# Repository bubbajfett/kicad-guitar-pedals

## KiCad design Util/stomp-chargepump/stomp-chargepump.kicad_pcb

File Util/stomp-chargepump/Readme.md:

# Chargepump/stomp board.

*  prevents reverse polarity
*  3pdt + led
*  -9v optional out
*  18v optional out
*  Both ICL7660 and LT1054

This has been tested but not thoroughly.    This layout is based on
several vero layout on Tagboardeffects.blogspot.com

2nd revision of this to use 4pin connectors for wiring simplicity

All registered trademarks are owned by their respective owners.

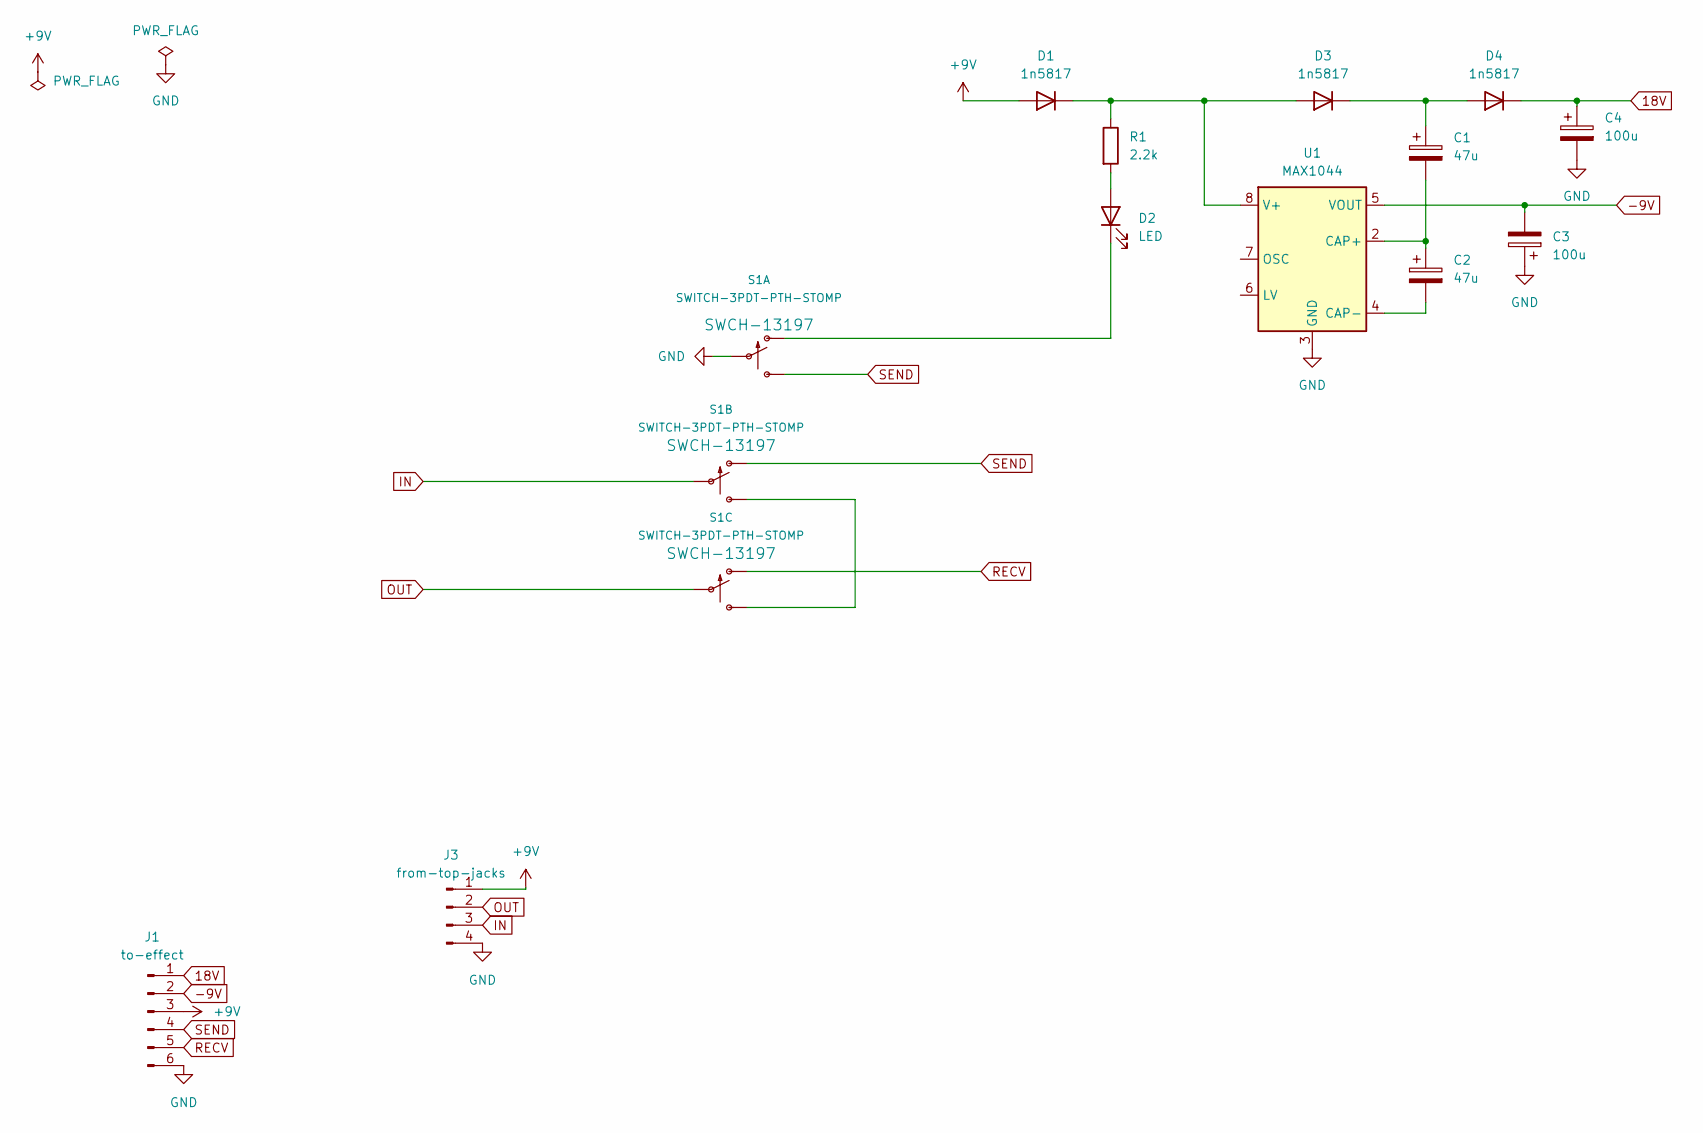
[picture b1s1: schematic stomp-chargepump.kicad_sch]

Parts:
C1, C2: 47u; CP_Radial_D5.0mm_P2.00mm
C3, C4: 100u; CP_Radial_D6.3mm_P2.50mm
D1, D3, D4: 1n5817; D_5W_P10.16mm_Horizontal
D2: LED; LED_D3.0mm
J1: to-effect; PinHeader_1x06_P2.54mm_Vertical
J3: from-top-jacks; PinHeader_1x04_P2.54mm_Vertical
R1: 2.2k; R_Axial_DIN0207_L6.3mm_D2.5mm_P10.16mm_Horizontal
S1: SWITCH-3PDT-PTH-STOMP; STOMP_SWITCH_3PDT
U1: MAX1044; DIP-8_W7.62mm_LongPads

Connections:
18V: C4.1, D4.1 (K), J1.1
+9V: D1.2 (A), J1.3, J3.1
-9V: C3.2, J1.2, U1.5 (VOUT)
GND: C3.1, C4.2, J1.6, J3.4, S1.P$2, U1.3 (GND)
IN: J3.3, S1.P$5
unnamed: D1.1 (K), D3.2 (A), R1.1, U1.8 (V+)
unnamed: D2.2 (A), R1.2
unnamed: D2.1 (K), S1.P$1 (O)
unnamed: C1.1, D3.1 (K), D4.2 (A)
unnamed: S1.P$6 (S), S1.P$9 (S)
unnamed: C1.2, C2.1, U1.2 (CAP+)
unnamed: C2.2, U1.4 (CAP-)
OUT: J3.2, S1.P$8
RECV: J1.5, S1.P$7 (O)
SEND: J1.4, S1.P$3 (S), S1.P$4 (O)

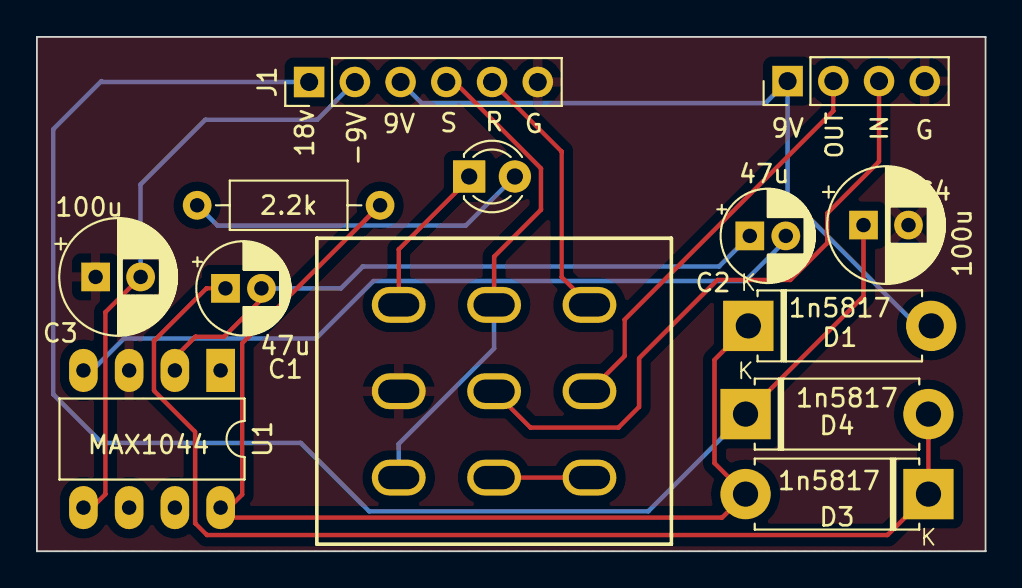
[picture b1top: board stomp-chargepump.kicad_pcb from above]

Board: 2 copper layers, 52.7 x 28.6 mm, 13 parts (0 on the bottom side), 15 nets.

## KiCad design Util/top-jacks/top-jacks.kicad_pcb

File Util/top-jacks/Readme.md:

# TOP Jacks

This is a pcb allowing the input, output and power jack to be mounted at the top of the enclosure, instead of having power at the top, and jacks mounted on the side.   This simplifies the wiring.   I put the diode on this as well so that all pedals get polarity protection.   The jacks used from taydaelectronics: 

6.35mm 1/4" Right Angle Mono Female Connector Thread Lock Panel Mount CK635008,  SKU: A-6976

For this to work and have it above the 16mm pots, you have to drill it as close
to the bottom of the enclosure as you can get.

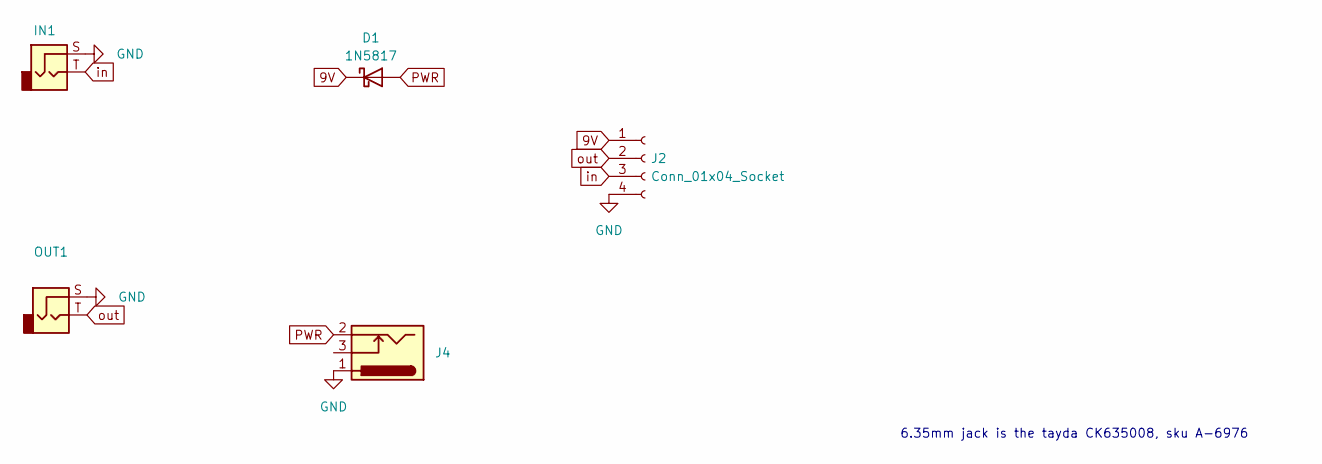
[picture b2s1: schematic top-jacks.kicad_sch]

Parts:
D1: 1N5817; D_DO-41_SOD81_P10.16mm_Horizontal
IN1: AudioJack3_dual_switch; 6.35mm-audio-jack
J2: Conn_01x04_Socket; PinHeader_1x04_P2.54mm_Vertical
J4: Barrel_Jack_Switch; BarrelJack_GCT_DCJ200-10-A_Horizontal
OUT1: AudioJack3_dual_switch; 6.35mm-audio-jack

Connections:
9V: D1.1 (K), J2.1
GND: IN1.S, J2.4, J4.1, OUT1.S
PWR: D1.2 (A), J4.2
in: IN1.T, J2.3
out: J2.2, OUT1.T

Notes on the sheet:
6.35mm jack is the tayda CK635008, sku A-6976

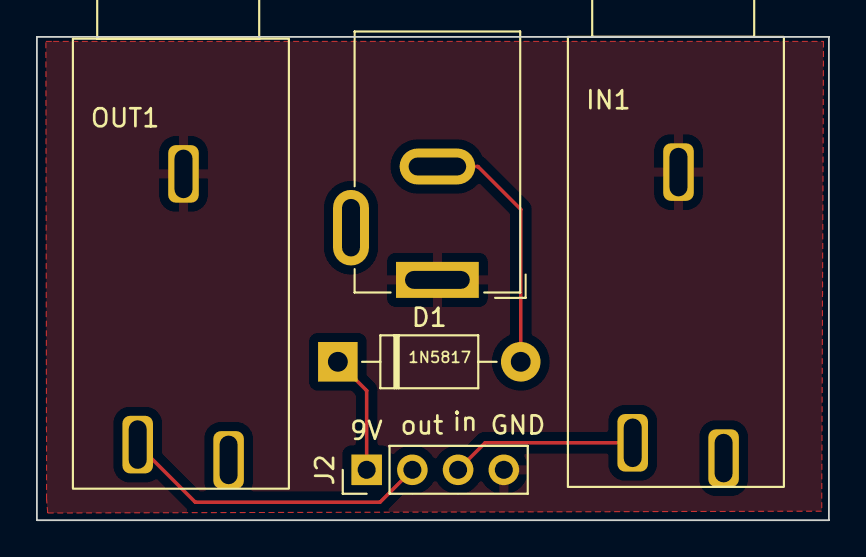
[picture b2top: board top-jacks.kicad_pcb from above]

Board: 2 copper layers, 44.0 x 26.8 mm, 5 parts (0 on the bottom side), 5 nets.
